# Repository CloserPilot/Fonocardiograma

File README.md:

# 🫀 Fonocardiograma

Sistema completo para **registro, visualización y análisis de fonocardiogramas (PCG)** que combina hardware electrónico, firmware para microcontrolador y aplicación móvil Android.
---

## 📌 Descripción del proyecto

Este proyecto entrega todas las partes necesarias para **reconstruir el dispositivo de prueba del fonocardiograma**, integrando adquisición de señal, transmisión inalámbrica y visualización multiplataforma.

Incluye:

- **Hardware** — diseños electrónicos y PCB para captura de señales acústicas cardiacas.
- **Firmware** — programa embebido para microcontrolador que adquiere y transmite datos.
- **Software móvil** — aplicación Android para comunicación con el hardware, visualización y exposición de datos en red local.
- **Documentación** — manuales y lista de partes.

Cada componente está diseñado para ser **independiente, reutilizable y extensible**.

---

## 📁 Estructura del repositorio

### 📦 APK/
Archivo **.apk instalable** de la aplicación Android, permitiendo su uso sin necesidad de compilación.

---

### 🛠 Circuitos/
Diseños electrónicos desarrollados en **KiCAD**:
- Esquemático del sistema.
- Diseño de PCB y capas correspondientes.

---

### 📲 Codigo AndroidStudio/
Proyecto completo de la aplicación Android desarrollado en **Android Studio**:
- Código fuente en Java.
- Interfaz de visualización de la señal.
- Gestión de conexión Bluetooth y red local.

La aplicación permite:
- Visualizar el fonocardiograma en el dispositivo móvil.
- Exponer la señal mediante **red local (LAN)** para su visualización en cualquier navegador web dentro de la misma red.

---

### 🧠 Codigo Arduino/
Código fuente para el microcontrolador (**ATTiny85 / AVR / Arduino compatible**):
- Configuración de ADC y adquisición de señal.
- Manejo de buffers de datos.
- Comunicación serial hacia el módulo Bluetooth **HC-05**.
- Scripts auxiliares para pruebas y depuración.

Este firmware es responsable de **capturar la señal acústica cardiaca y transmitirla a la aplicación móvil**.

---

### 📄 Documentacion.pdf
Documento técnico que describe:
- Objetivo del proyecto.
- Funcionamiento general del sistema.
- Interconexión entre hardware, firmware y aplicación.

---

### 🧾 Manual de usuario.pdf
Guía práctica para:
- Montaje del hardware.
- Uso del sistema de adquisición.
- Funcionamiento de la aplicación Android.
- Descripción de los módulos que integran la app.

---

### 📊 Lista de partes y costos.xlsx
Listado de componentes con:
- Cantidades requeridas.
- Costos estimados.
- Referencias de proveedores.

Facilita la reproducción del dispositivo.

---

## 📌 Uso del sistema

1. **Montaje de hardware**  
   Ensambla el circuito utilizando los esquemáticos de `Circuitos/` y la lista de partes.

2. **Carga de firmware**  
   Programa el microcontrolador con el código de `Codigo Arduino/`.

3. **Aplicación Android**  
   - Instala la app desde `APK/` o compílala desde `Codigo AndroidStudio/`.
   - Conecta el dispositivo vía Bluetooth.

4. **Visualización**  
   - Visualiza el fonocardiograma directamente en el teléfono.
   - Activa el **modo LAN** para acceder a la señal desde cualquier navegador web dentro de la misma red local (PC, tablet u otro dispositivo).

---

## 🎯 Casos de uso

- Prácticas académicas de bioinstrumentación.
- Análisis y estudio de bioseñales acústicas.
- Prototipado de sistemas biomédicos.
- Demostraciones de integración hardware–software–red.

---

## 🧩 Consideraciones

Este sistema **no sustituye equipos médicos certificados**. Está destinado a fines educativos, experimentales y de prototipado.

---

## 📜 Licencia

Licencia de código abierto (ver archivo `LICENSE` para detalles).

---

## 🤝 Contribuciones

Se aceptan mejoras en:
- Firmware
- Diseño electrónico
- Aplicación Android
- Visualización y análisis de señal

Usa *issues* o *pull requests* para proponer cambios.

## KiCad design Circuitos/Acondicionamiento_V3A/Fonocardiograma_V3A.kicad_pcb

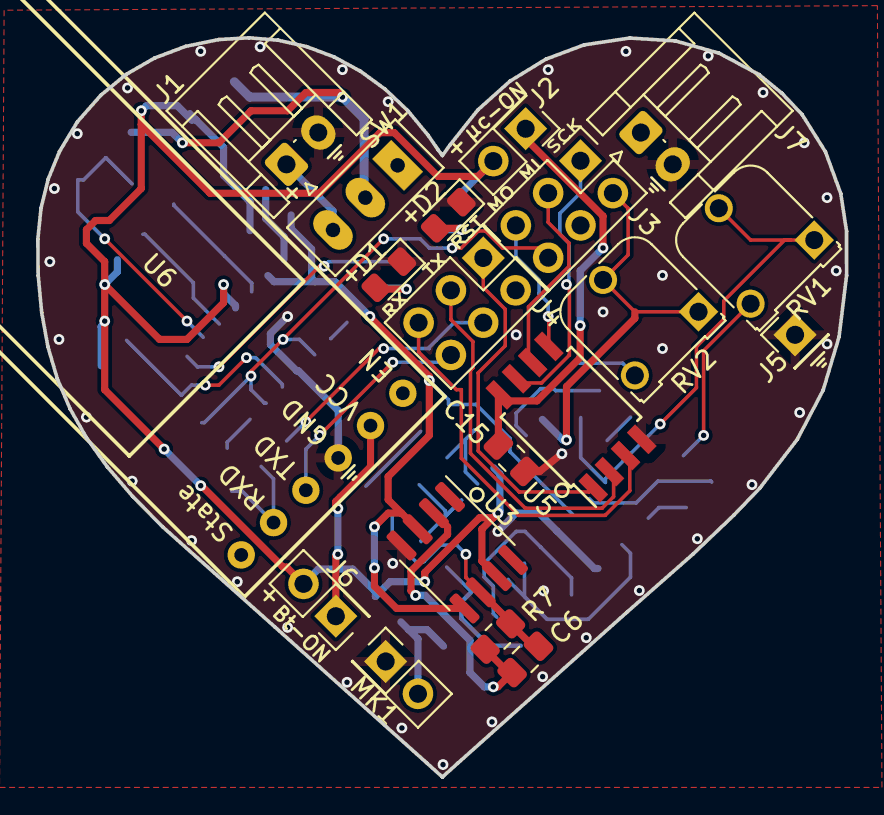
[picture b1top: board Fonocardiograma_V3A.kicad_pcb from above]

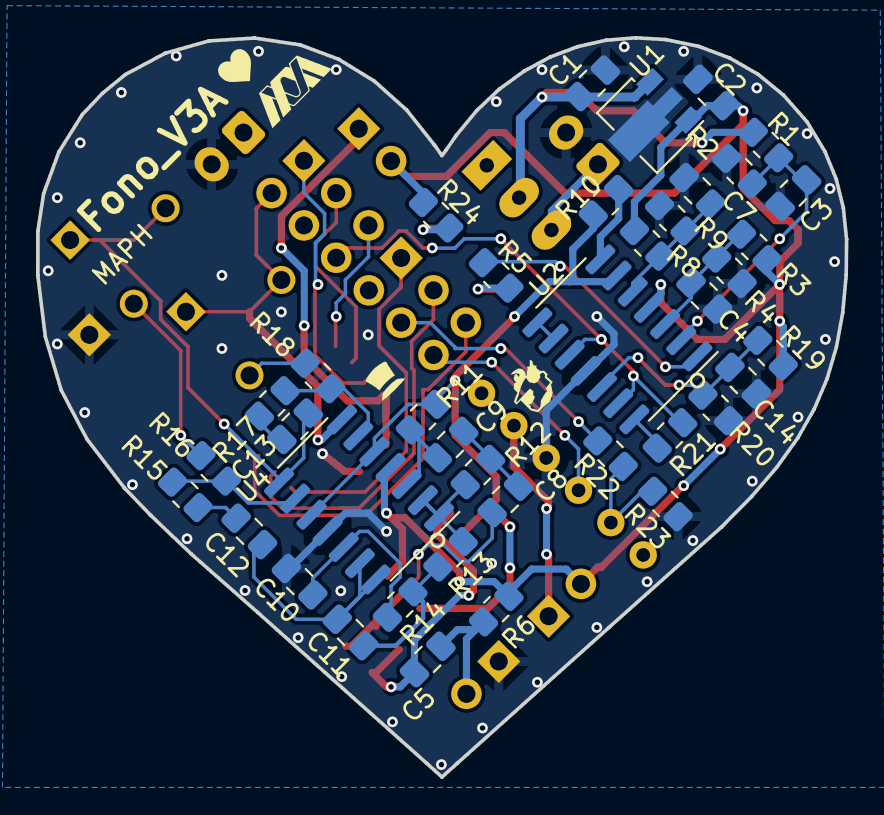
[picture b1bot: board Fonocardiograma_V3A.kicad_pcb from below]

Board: 2 copper layers, 44.9 x 41.1 mm, 58 parts (39 on the bottom side), 44 nets.

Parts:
C1: 330nf; C_0805_2012Metric_Pad1.18x1.45mm_HandSolder
C2: 100nf; C_0805_2012Metric_Pad1.18x1.45mm_HandSolder
C3, C4, C7, C9, C14, C15: 470n; C_0805_2012Metric_Pad1.18x1.45mm_HandSolder
C5, C8, C12, C13: 2.2u; C_0805_2012Metric_Pad1.18x1.45mm_HandSolder
C6: 3.3n; C_0805_2012Metric_Pad1.18x1.45mm_HandSolder
C10: 22n; C_0805_2012Metric_Pad1.18x1.45mm_HandSolder
C11: 100n; C_0805_2012Metric_Pad1.18x1.45mm_HandSolder
D1, D2: LED; LED_0805_2012Metric_Pad1.15x1.40mm_HandSolder
J1, J7: Conn_01x02; JST_EH_S2B-EH_1x02_P2.50mm_Horizontal
J2, J6: Conn_02x01; PinHeader_2x01_P2.54mm_Vertical
J3, J4: Conn_02x03_Odd_Even; PinHeader_2x03_P2.54mm_Vertical
J5: Conn_01x01; PinHeader_1x01_P2.54mm_Vertical
MK1: Microphone_Condenser; PinHeader_2x01_P2.54mm_Vertical
R1, R3, R4: 100K; R_0805_2012Metric_Pad1.20x1.40mm_HandSolder
R2: 51K; R_0805_2012Metric_Pad1.20x1.40mm_HandSolder
R5, R24: 330; R_0805_2012Metric_Pad1.20x1.40mm_HandSolder
R6: 6.8k; R_0805_2012Metric_Pad1.20x1.40mm_HandSolder
R7: 39k; R_0805_2012Metric_Pad1.20x1.40mm_HandSolder
R8: 75k; R_0805_2012Metric_Pad1.20x1.40mm_HandSolder
R9: 51k; R_0805_2012Metric_Pad1.20x1.40mm_HandSolder
R10, R21: 50; R_0805_2012Metric_Pad1.20x1.40mm_HandSolder
R11: 15k; R_0805_2012Metric_Pad1.20x1.40mm_HandSolder
R12: 4.7k; R_0805_2012Metric_Pad1.20x1.40mm_HandSolder
R13: 1.2k; R_0805_2012Metric_Pad1.20x1.40mm_HandSolder
R14, R15, R16, R17, R18: 10k; R_0805_2012Metric_Pad1.20x1.40mm_HandSolder
R19, R22: 100k; R_0805_2012Metric_Pad1.20x1.40mm_HandSolder
R20, R23: 200k; R_0805_2012Metric_Pad1.20x1.40mm_HandSolder
RV1, RV2: 100k; Potentiometer_Runtron_RM-065_Vertical
SW1: SW_SPDT; SW_Slide_1P2T_SS12D00G4
U1: L78L05_SOT89; SOT-89-3
U2, U4: LM324; SOIC-14_3.9x8.7mm_P1.27mm
U3: AD623; SOIC-8_3.9x4.9mm_P1.27mm
U5: ATtiny85-20S; SOIC-8W_5.3x5.3mm_P1.27mm
U6: HC-05

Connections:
2V Vref: R10.2, R11.2, U2.6 (-), U3.3 (+), U3.5 (Ref), U4.5 (+), U4.10 (+)
+5V: C2.1, J2.2, J6.2, R3.2, R6.2, R8.2, R19.2, R24.2, U1.1 (OUT), U2.4 (V+), U3.7 (Vs+), U4.4 (V+)
+9V: C1.1, R1.2, SW1.2 (B), U1.3 (IN)
ADC1: J3.2, RV2.1, RV2.2, U4.7
AREF: J3.6, R21.2, U2.10 (+), U2.13 (-)
GND: C1.2, C2.2, C3.1, C4.1, C7.1, C10.1, C14.1, C15.1, D1.1 (K), D2.1 (K), J1.2, J5.1, J7.2, MK1.1 (-), R2.1, R4.1, R9.1, R20.1, R23.2, U1.2 (GND), U2.11 (V-), U3.4 (Vs-), U4.11 (V-), U5.4 (GND), U6.4 (GND)
MISO: J3.3, U5.6 (PB1)
MOSI/AREF: J3.5, U5.5 (AREF/PB0)
unnamed: C6.2, C8.2, R7.1, U3.6
unnamed: C8.1, C9.1, R12.1
unnamed: C11.1, R13.2, R14.1
unnamed: C12.1, R15.2
unnamed: C13.1, R17.2
unnamed: C13.2, RV1.1, RV1.2, U4.8
unnamed: D1.2 (A), R5.2
unnamed: D2.2 (A), R24.1
unnamed: J1.1, SW1.3 (C)
unnamed: C15.2, J2.1, U5.8 (VCC)
unnamed: J6.1, U6.5 (VCC)
unnamed: C5.1, MK1.2 (+), R6.1
unnamed: R5.1, U2.1
unnamed: R10.1, U2.7
unnamed: R16.1, RV1.3
unnamed: R18.1, RV2.3
unnamed: R21.1, U2.14
unnamed: C4.2, R3.1, R4.2, U2.3 (+)
unnamed: C3.2, R1.1, R2.2, U2.2 (-)
unnamed: C7.2, R8.1, R9.2, U2.5 (+)
unnamed: U2.8, U2.9 (-)
unnamed: C14.2, R19.1, R20.2, U2.12 (+)
unnamed: C5.2, C6.1, R7.2, U3.2 (-)
unnamed: C9.2, R11.1, U4.3 (+)
unnamed: R12.2, R13.1, U4.1, U4.2 (-)
unnamed: R17.1, R18.2, U4.6 (-)
unnamed: R15.1, R16.2, U4.9 (-)
unnamed: C10.2, R14.2, U4.12 (+)
unnamed: C11.2, C12.2, U4.13 (-), U4.14
unnamed: R22.2, R23.1, U6.2 (RXD)
RESET: J4.1, U5.1 (~RESET/PB5)
RX: J4.5, U5.3 (XTAL2/PB4)
RXD: J4.4, R22.1
SCK/ADC1: J3.1, U5.7 (PB2)
TX: J4.3, U5.2 (XTAL1/PB3)
TXD: J4.6, U6.3 (TXD)

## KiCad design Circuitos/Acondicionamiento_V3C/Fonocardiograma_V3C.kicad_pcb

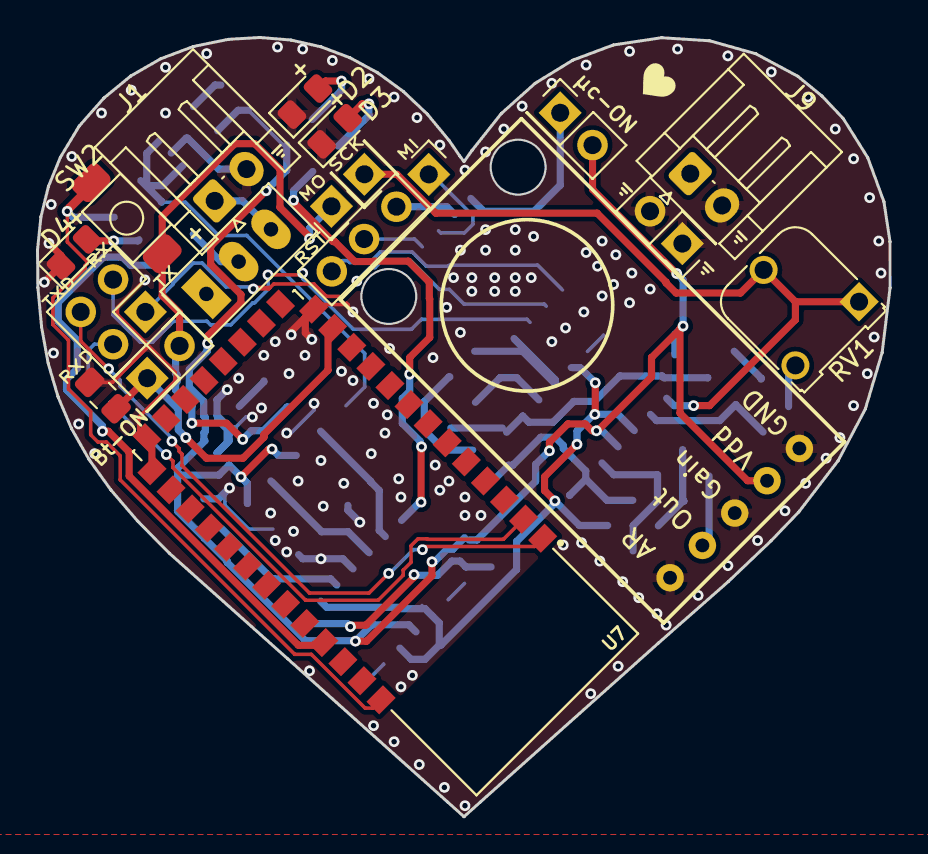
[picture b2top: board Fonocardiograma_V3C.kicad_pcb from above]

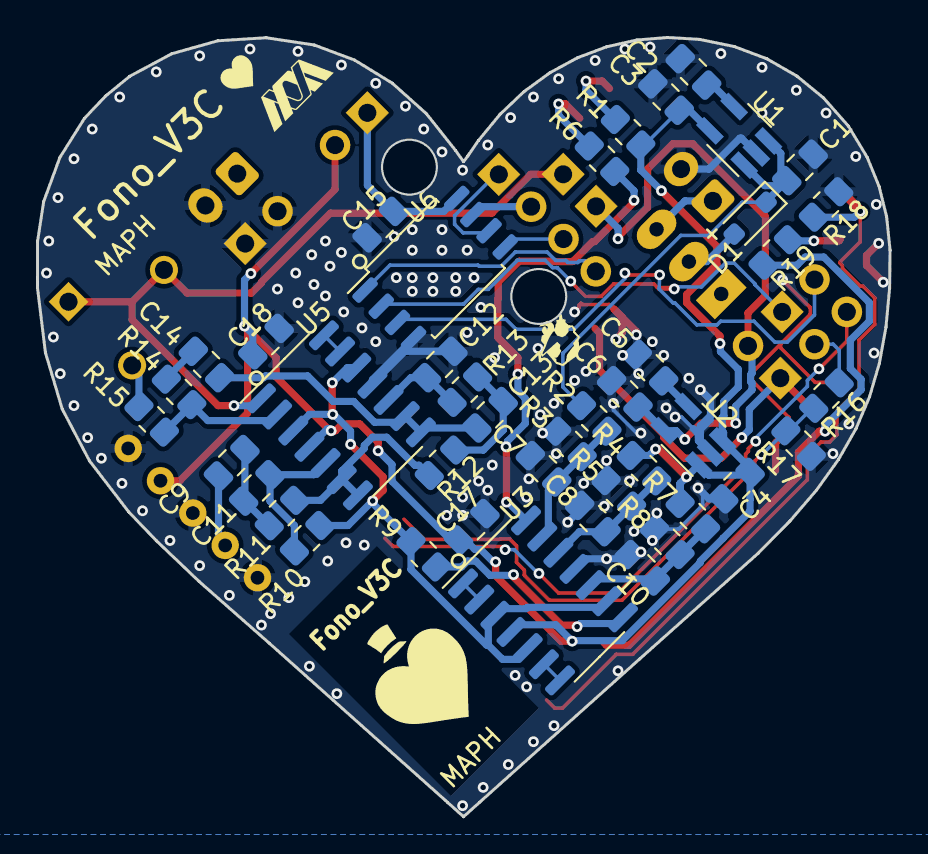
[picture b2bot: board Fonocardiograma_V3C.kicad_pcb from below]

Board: 2 copper layers, 47.4 x 43.3 mm, 60 parts (42 on the bottom side), 44 nets.

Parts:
C1, C4: 1uf; C_0805_2012Metric_Pad1.18x1.45mm_HandSolder
C2, C5: 100nf; C_0805_2012Metric_Pad1.18x1.45mm_HandSolder
C3, C6: 2.2uf; C_0805_2012Metric_Pad1.18x1.45mm_HandSolder
C7, C8, C10, C11: 470n; C_0805_2012Metric_Pad1.18x1.45mm_HandSolder
C9, C14: 2.2u; C_0805_2012Metric_Pad1.18x1.45mm_HandSolder
C12: 22n; C_0805_2012Metric_Pad1.18x1.45mm_HandSolder
C13, C15, C16, C17, C18: 100n; C_0805_2012Metric_Pad1.18x1.45mm_HandSolder
D1: 1N5819WS; D_SOD-323_HandSoldering
D2, D3, D4: LED; LED_0805_2012Metric_Pad1.15x1.40mm_HandSolder
J1, J9: Conn_01x02; JST_EH_S2B-EH_1x02_P2.50mm_Horizontal
J2, J7, J8: Conn_02x01; PinHeader_2x01_P2.54mm_Vertical
J3: Conn_01x04; PinHeader_1x04_P2.54mm_Vertical
J4, J5: Conn_01x01; PinHeader_1x01_P2.54mm_Vertical
J6: Conn_02x02_Odd_Even; PinHeader_2x02_P2.54mm_Vertical
R1, R6, R18, R19: 1k; R_0805_2012Metric_Pad1.20x1.40mm_HandSolder
R2, R4: 100K; R_0805_2012Metric_Pad1.20x1.40mm_HandSolder
R3: 51K; R_0805_2012Metric_Pad1.20x1.40mm_HandSolder
R5, R7: 75k; R_0805_2012Metric_Pad1.20x1.40mm_HandSolder
R8: 51k; R_0805_2012Metric_Pad1.20x1.40mm_HandSolder
R9: 50; R_0805_2012Metric_Pad1.20x1.40mm_HandSolder
R10: 15k; R_0805_2012Metric_Pad1.20x1.40mm_HandSolder
R11: 4.7k; R_0805_2012Metric_Pad1.20x1.40mm_HandSolder
R12: 1.2k; R_0805_2012Metric_Pad1.20x1.40mm_HandSolder
R13, R14, R15: 10k; R_0805_2012Metric_Pad1.20x1.40mm_HandSolder
R16: 100k; R_0805_2012Metric_Pad1.20x1.40mm_HandSolder
R17: 200k; R_0805_2012Metric_Pad1.20x1.40mm_HandSolder
RV1: 100k; Potentiometer_Runtron_RM-065_Vertical
SW1: SW_SPDT; SW_Slide_1P2T_SS12D00G4
SW2: SW_Push; BT_3x4x2h mm
U1: LP2985-5.0; SOT-23-5_HandSoldering
U2: LP2985-3.3; SOT-23-5_HandSoldering
U3, U5: LM324; SOIC-14_3.9x8.7mm_P1.27mm
U4: MAX9814; MAX9814-Adafruit
U6: ATtiny85-20S; SOP-8_5.28x5.23mm_P1.27mm
U7: HC-05; XCVR_HC-05

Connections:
2V Vref: R9.2, R10.2, U3.3 (+), U3.5 (+), U3.9 (-), U5.3 (+), U5.12 (+)
+3.3V: C6.1, J5.1, J8.2, SW2.2, U2.5 (VOUT)
+5V: C3.1, C4.1, C17.1, C18.1, J2.2, R1.1, R4.2, R7.2, U1.5 (VOUT), U2.1 (VIN), U2.3 (ON/~OFF), U3.4 (V+), U4.4 (VDD), U5.4 (V+)
+9V: C1.1, D1.1 (K), R2.2, U1.1 (VIN), U1.3 (ON/~OFF)
ADC1: J4.1, RV1.1, RV1.2, U5.1
GND: C1.2, C2.2, C3.2, C4.2, C5.2, C6.2, C7.1, C8.1, C10.1, C12.1, C15.1, C16.2, C17.2, C18.2, D2.1 (K), D3.1 (K), D4.1 (K), J1.2, J7.1, J7.2, J9.2, R3.1, R5.1, R8.1, R17.1, R18.2, U1.2 (GND), U2.2 (GND), U3.11 (V-), U4.1 (AR), U4.3 (GAIN), U4.5 (GND), U5.11 (V-), U6.4 (GND), U7.13 (GND), U7.21 (GND), U7.22 (GND)
MISO: J3.1, U6.6 (PB1)
MOSI/AREF: J3.3, U6.5 (AREF/PB0)
unnamed: C9.2, C11.1, R11.1
unnamed: C13.1, R12.2, R13.1
unnamed: C14.1, R14.2
unnamed: D1.2 (A), SW1.2 (B)
unnamed: D2.2 (A), R1.2
unnamed: D3.2 (A), R6.2
unnamed: D4.2 (A), R19.2
unnamed: J1.1, SW1.3 (C)
unnamed: C15.2, J2.1, U6.8 (VCC)
unnamed: C16.1, J8.1, U7.12 (3.3_VCC)
unnamed: R6.1, U3.14
unnamed: R9.1, U3.8
unnamed: R15.1, RV1.3
unnamed: C2.1, U1.4 (BP)
unnamed: C5.1, U2.4 (BP)
unnamed: U3.1, U3.2 (-)
unnamed: U3.6 (-), U3.7
unnamed: C10.2, R7.1, R8.2, U3.10 (+)
unnamed: C8.2, R4.1, R5.2, U3.12 (+)
unnamed: C7.2, R2.1, R3.2, U3.13 (-)
unnamed: C9.1, U4.2 (OUT)
unnamed: R14.1, R15.2, U5.2 (-)
unnamed: C11.2, R10.1, U5.5 (+)
unnamed: R11.2, R12.1, U5.6 (-), U5.7
unnamed: C12.2, R13.2, U5.10 (+)
unnamed: C13.2, C14.2, U5.8, U5.9 (-)
unnamed: U5.13 (-), U5.14
unnamed: R19.1, U7.31 (PIO[8])
unnamed: R18.1, SW2.1, U7.34 (PIO[11])
unnamed: R16.1, R17.2, U7.2 (UART-RX)
RESET: J3.4, U6.1 (~RESET/PB5)
RX: J6.3, U6.3 (XTAL2/PB4)
RXD: J6.2, R16.2
SCK/ADC1: J3.2, U6.7 (PB2)
TX: J6.1, U6.2 (XTAL1/PB3)
TXD: J6.4, U7.1 (UART-TX)

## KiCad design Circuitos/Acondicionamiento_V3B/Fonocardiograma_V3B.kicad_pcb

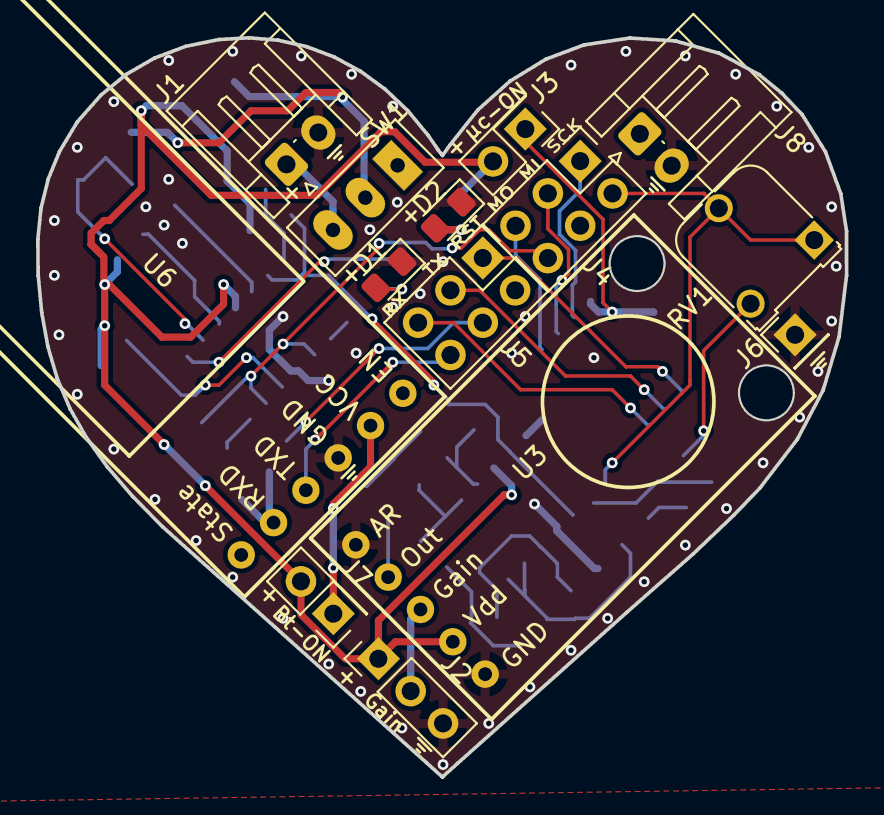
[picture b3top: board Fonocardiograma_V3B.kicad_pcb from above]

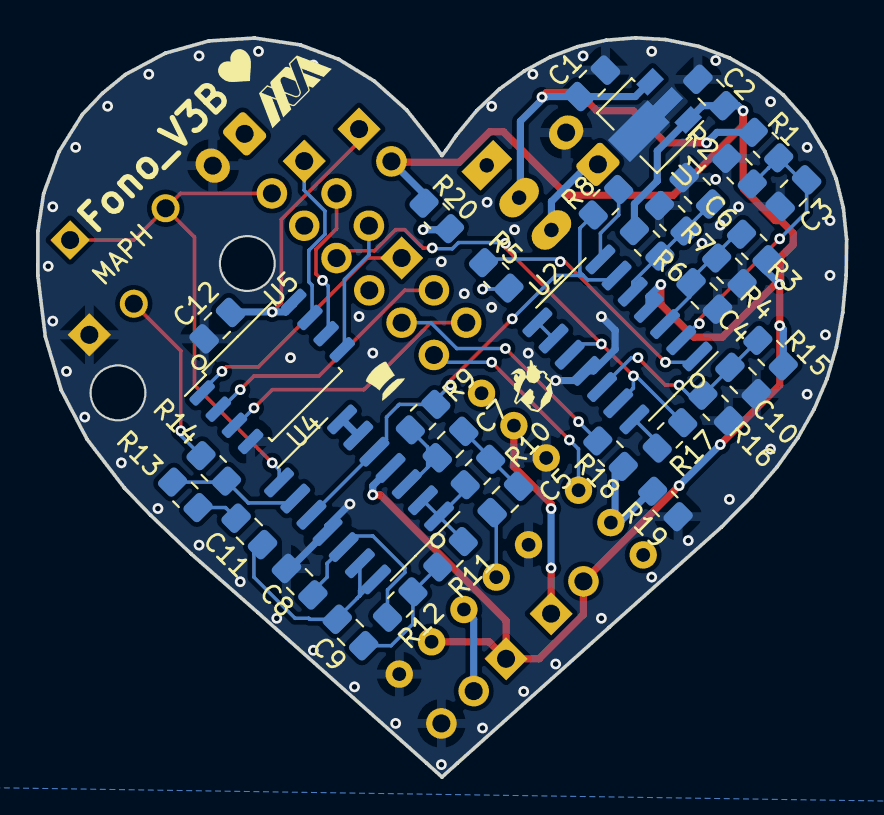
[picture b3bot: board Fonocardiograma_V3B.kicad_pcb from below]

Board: 2 copper layers, 44.9 x 41.1 mm, 50 parts (36 on the bottom side), 40 nets.

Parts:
C1: 330nf; C_0805_2012Metric_Pad1.18x1.45mm_HandSolder
C2: 100nf; C_0805_2012Metric_Pad1.18x1.45mm_HandSolder
C3, C4, C6, C7, C10: 470n; C_0805_2012Metric_Pad1.18x1.45mm_HandSolder
C5, C11: 2.2u; C_0805_2012Metric_Pad1.18x1.45mm_HandSolder
C8: 22n; C_0805_2012Metric_Pad1.18x1.45mm_HandSolder
C9, C12: 100n; C_0805_2012Metric_Pad1.18x1.45mm_HandSolder
D1, D2: LED; LED_0805_2012Metric_Pad1.15x1.40mm_HandSolder
J1, J8: Conn_01x02; JST_EH_S2B-EH_1x02_P2.50mm_Horizontal
J2: Conn_01x03; PinHeader_1x03_P2.54mm_Vertical
J3, J7: Conn_02x01; PinHeader_2x01_P2.54mm_Vertical
J4, J5: Conn_02x03_Odd_Even; PinHeader_2x03_P2.54mm_Vertical
J6: Conn_01x01; PinHeader_1x01_P2.54mm_Vertical
R1, R3, R4, R15: 100K; R_0805_2012Metric_Pad1.20x1.40mm_HandSolder
R2: 51K; R_0805_2012Metric_Pad1.20x1.40mm_HandSolder
R5, R20: 330; R_0805_2012Metric_Pad1.20x1.40mm_HandSolder
R6: 75k; R_0805_2012Metric_Pad1.20x1.40mm_HandSolder
R7: 51k; R_0805_2012Metric_Pad1.20x1.40mm_HandSolder
R8, R17: 50; R_0805_2012Metric_Pad1.20x1.40mm_HandSolder
R9: 15k; R_0805_2012Metric_Pad1.20x1.40mm_HandSolder
R10: 4.7k; R_0805_2012Metric_Pad1.20x1.40mm_HandSolder
R11: 1.2k; R_0805_2012Metric_Pad1.20x1.40mm_HandSolder
R12, R13, R14: 10k; R_0805_2012Metric_Pad1.20x1.40mm_HandSolder
R16: 200K; R_0805_2012Metric_Pad1.20x1.40mm_HandSolder
R18: 100k; R_0805_2012Metric_Pad1.20x1.40mm_HandSolder
R19: 200k; R_0805_2012Metric_Pad1.20x1.40mm_HandSolder
RV1: 100k; Potentiometer_Runtron_RM-065_Vertical
SW1: SW_SPDT; SW_Slide_1P2T_SS12D00G4
U1: L78L05_SOT89; SOT-89-3
U2, U4: LM324; SOIC-14_3.9x8.7mm_P1.27mm
U3: MAX9814; MAX9814-Adafruit
U5: ATtiny85-20S; SOP-8_5.28x5.23mm_P1.27mm
U6: HC-05

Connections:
2V Vref: R8.2, R9.2, U2.6 (-), U4.5 (+), U4.10 (+)
+5V: C2.1, J2.1, J3.2, J7.2, R3.2, R6.2, R15.2, R20.1, U1.1 (OUT), U2.4 (V+), U3.4 (VDD), U4.4 (V+)
+9V: C1.1, R1.2, SW1.2 (B), U1.3 (IN)
ADC1: J4.2, RV1.1, RV1.2, U4.8
AREF: J4.6, R17.2, U2.10 (+), U2.13 (-)
GAIN: J2.2, U3.3 (GAIN)
GND: C1.2, C2.2, C3.1, C4.1, C6.1, C8.1, C10.1, C12.1, D1.1 (K), D2.1 (K), J1.2, J2.3, J6.1, J8.2, R2.1, R4.1, R7.1, R16.1, R19.1, U1.2 (GND), U2.11 (V-), U3.1 (AR), U3.5 (GND), U4.11 (V-), U5.4 (GND), U6.4 (GND)
MISO: J4.3, U5.6 (PB1)
MOSI/AREF: J4.5, U5.5 (AREF/PB0)
unnamed: C12.2, J3.1, U5.8 (VCC)
unnamed: J7.1, U6.5 (VCC)
unnamed: C5.2, C7.1, R10.1
unnamed: C9.1, R11.2, R12.1
unnamed: C11.1, R13.2
unnamed: D1.2 (A), R5.2
unnamed: D2.2 (A), R20.2
unnamed: J1.1, SW1.3 (C)
unnamed: R5.1, U2.1
unnamed: R8.1, U2.7
unnamed: R14.1, RV1.3
unnamed: R17.1, U2.14
unnamed: C4.2, R3.1, R4.2, U2.3 (+)
unnamed: C3.2, R1.1, R2.2, U2.2 (-)
unnamed: C6.2, R6.1, R7.2, U2.5 (+)
unnamed: U2.8, U2.9 (-)
unnamed: C10.2, R15.1, R16.2, U2.12 (+)
unnamed: C5.1, U3.2 (OUT)
unnamed: C7.2, R9.1, U4.3 (+)
unnamed: R10.2, R11.1, U4.1, U4.2 (-)
unnamed: U4.6 (-), U4.7
unnamed: R13.1, R14.2, U4.9 (-)
unnamed: C8.2, R12.2, U4.12 (+)
unnamed: C9.2, C11.2, U4.13 (-), U4.14
unnamed: R18.2, R19.2, U6.2 (RXD)
RESET: J5.1, U5.1 (~RESET/PB5)
RX: J5.5, U5.3 (XTAL2/PB4)
RXD: J5.4, R18.1
SCK/ADC1: J4.1, U5.7 (PB2)
TX: J5.3, U5.2 (XTAL1/PB3)
TXD: J5.6, U6.3 (TXD)

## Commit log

2023-06-26 Add Files
    *Circuitos
    *Codigo AndroidStudio
    *Codigo Arduino
2023-06-26 Basura quitada
2023-06-26 Reporte
    Actualizacion del reporte
2023-06-26 Reporte actualizacion
2023-06-27 Reporte y codigo
    Codigo comentado y reporte actualizado
2023-06-27 Bugs Errors
2023-06-28 Reporte
    Correccion de errores y reporte
2023-06-28 Reporte actualizacion
    Mas reporte, siu
2023-06-28 Reporte
    Mas cosas
2023-06-29 Final
    Push final de PT, bye bye hasta la proxima
2023-06-30 BaudRate LAN
    BaudRate LAN y correción de errores
2023-06-30 Manual y APK
2023-06-30 Costos
2023-07-07 update documentacion
2026-02-01 Clean up README by removing duplicates
    Removed duplicate images and extra lines from README.
